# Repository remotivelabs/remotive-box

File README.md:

# RemotiveBox

[RemotiveBroker](https://remotivelabs.com) runs on the hardware of your choice. We have a growing list of [reference kits](https://remotivelabs.com/downloads-documentations/#section-referense-kit)
to ensure that getting started is quick and simple.

Here you can find STL files to print your own RemotiveBox.

Simply import the files from the folder [3D-model/STL](3D-model/STL) into your favorite 3D printer/slicing tool.

## Components

- Raspberry Pi 4 (4GB)
- [Seeed Studio](https://wiki.seeedstudio.com/2-Channel-CAN-BUS-FD-Shield-for-Raspberry-Pi/)
- Mounting kit (D-SUB mountings), [41011082](https://www.electrokit.com/en/product/mounting-kit-d-sub-13mm/)
- Rubber foot, [41001130](https://www.electrokit.com/en/product/rubber-foot-11x5-mm/)

A PCB has been developed to connect the D-sub and banana connectors to the Raspberry Pi inside the box. This PCB can be produced and assebled by [jlcpcb.com](https://cart.jlcpcb.com/quote) by uploading the [gerber files](Adapter_PCB_/Gerber). 
The banana connectors need to be purchased and soldered separetely from  [farnell.com](https://www.farnell.com)
- [Red](https://se.farnell.com/multicomp/24-243-1/banana-socket-20a-4mm-pcb-red/dp/1698982?ICID=I-HP-STM7REC-RP-3)
- [Black](https://se.farnell.com/multicomp/24-243-2/receptacle-20a-4mm-pcb-solder/dp/1698983)

## Gallery

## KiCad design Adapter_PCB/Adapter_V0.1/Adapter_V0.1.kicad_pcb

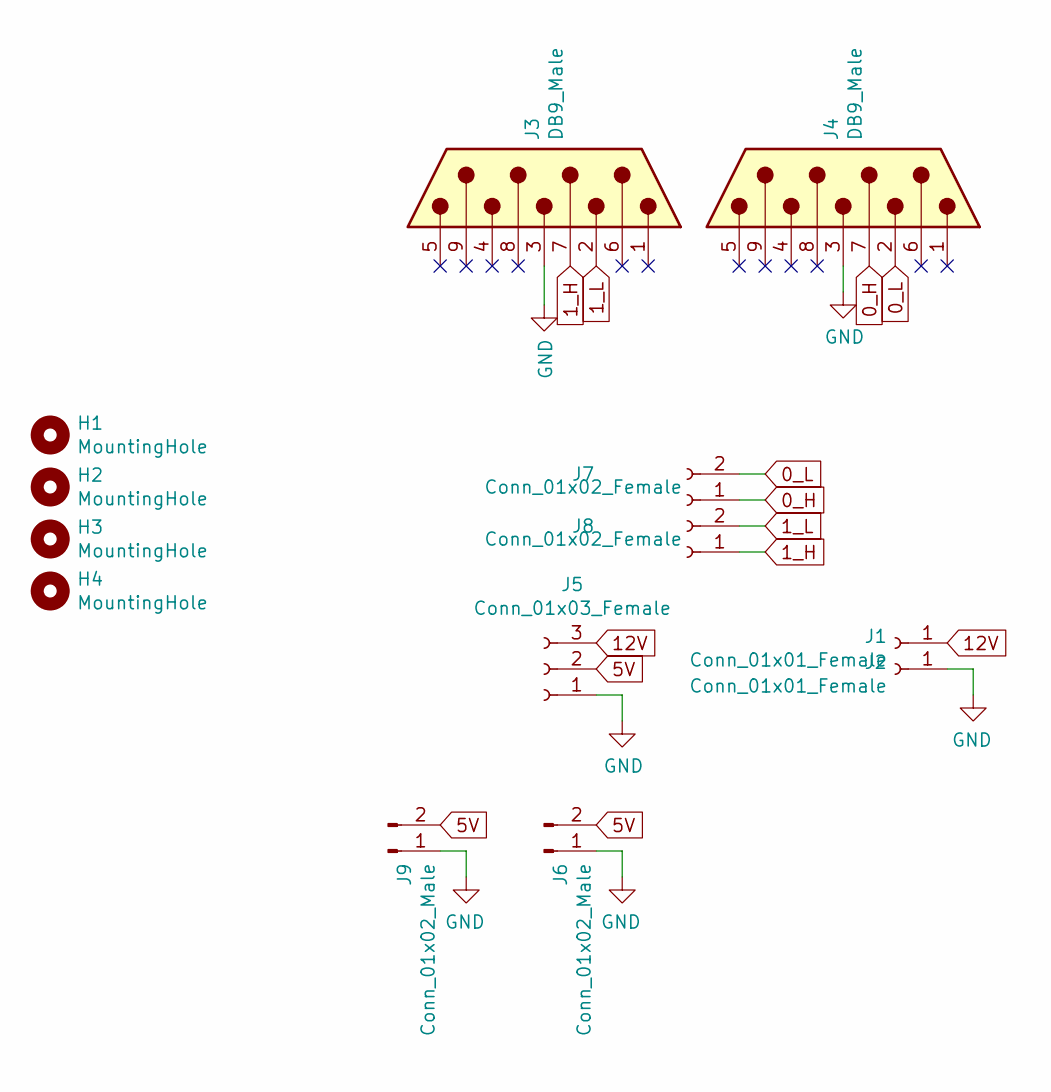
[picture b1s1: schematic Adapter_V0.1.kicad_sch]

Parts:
H1, H2, H3, H4: MountingHole; MountingHole_3.2mm_M3
J1, J2: Conn_01x01_Female; Banana_Jack
J3, J4: DB9_Male; DSUB-9_Male_Horizontal_P2.77x2.84mm_EdgePinOffset7.70mm_Hou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
J5: Conn_01x03_Female; TerminalBlock_Phoenix_MKDS-1,5-3-5.08_1x03_P5.08mm_Horizont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
J6: Conn_01x02_Male; JST_EH_B2B-EH-A_1x02_P2.50mm_Vertical
J7, J8: Conn_01x02_Female; TerminalBlock_Phoenix_MKDS-1,5-2-5.08_1x02_P5.08mm_Horizont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
J9: Conn_01x02_Male; TerminalBlock_Phoenix_MKDS-1,5-2-5.08_1x02_P5.08mm_Horizont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

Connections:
0_H: J4.7, J7.1
0_L: J4.2, J7.2
1_H: J3.7, J8.1
1_L: J3.2, J8.2
5V: J5.2, J6.2, J9.2
12V: J1.1, J5.3
GND: J2.1, J3.3, J4.3, J5.1, J6.1, J9.1

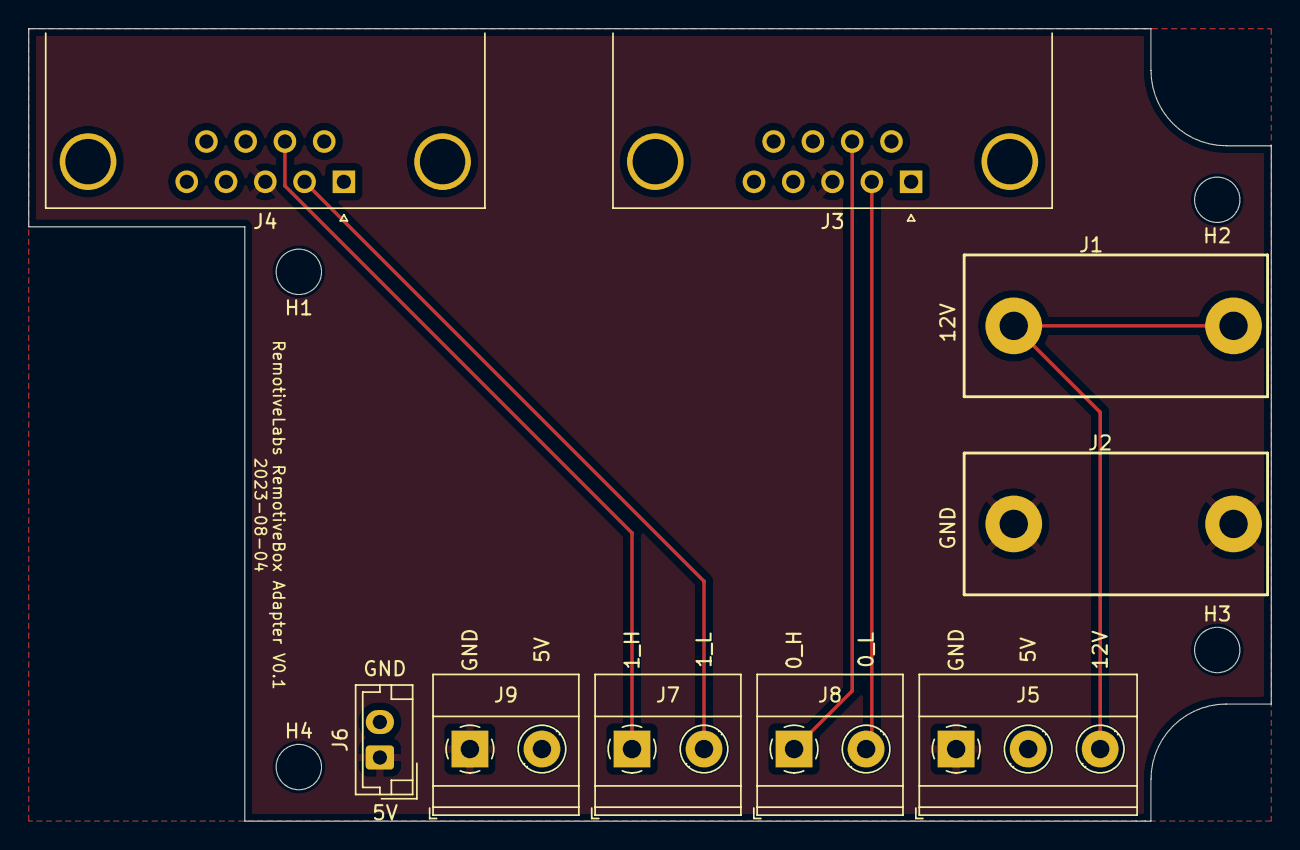
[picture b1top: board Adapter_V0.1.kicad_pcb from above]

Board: 2 copper layers, 87.6 x 55.9 mm, 13 parts (0 on the bottom side), 7 nets.

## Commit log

2023-03-13 Remotive Box DIY 3D kit documentation
    A copy of contents from the deprecated repository
    https://github.com/beamylabs/beamylabs-start/tree/master/beamyone/
2023-12-18 Update README.md
    Updated link to electrokit
2024-03-21 Added adapter PCB files and new 3d models, and removed the old ones. The was changed accordingly
2024-08-07 update images
